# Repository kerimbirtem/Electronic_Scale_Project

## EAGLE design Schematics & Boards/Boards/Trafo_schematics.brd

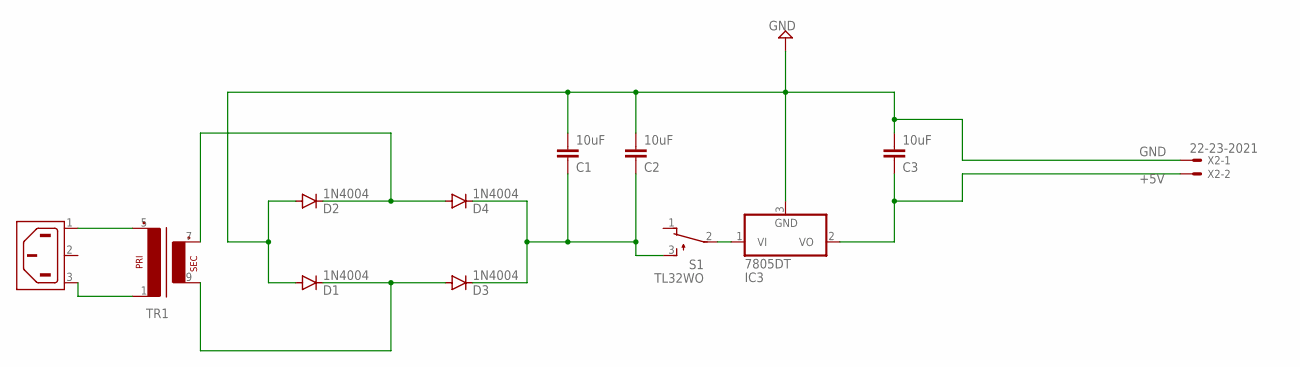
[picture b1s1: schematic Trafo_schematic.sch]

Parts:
C1, C2, C3: 10uF; C2.5-2
D1, D2, D3, D4: 1N4004; DO41-10
IC3: 7805DT; TO252
S1: TL32WO; TL3XWO
TR1: EI30-1
X1: 6ESRM-P
X2: 22-23-2021

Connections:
+5V: C3.1, IC3.2 (VO), X2.2
GND: C1.2, C2.2, C3.2, D1.A, D2.A, IC3.3 (GND), X2.1
unnamed: D1.C, D3.A, TR1.9 (S4)
unnamed: D2.C, D4.A, TR1.7 (S3)
unnamed: TR1.1, X1.3 (AC2)
unnamed: TR1.5 (P2), X1.1 (AC1)
unnamed: C1.1, C2.1, D3.C, D4.C, S1.3 (S)
unnamed: IC3.1 (VI), S1.2

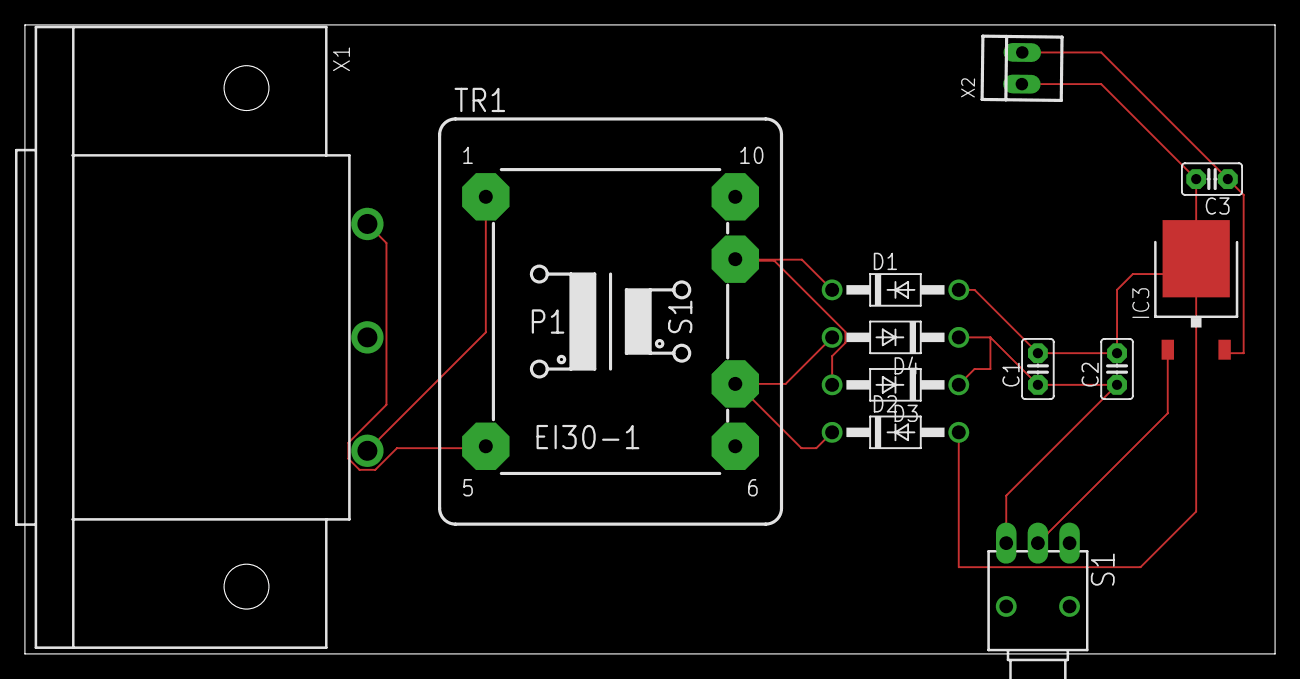
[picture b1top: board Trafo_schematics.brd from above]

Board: 2 copper layers, 100.3 x 50.5 mm, 12 parts (0 on the bottom side), 8 nets.

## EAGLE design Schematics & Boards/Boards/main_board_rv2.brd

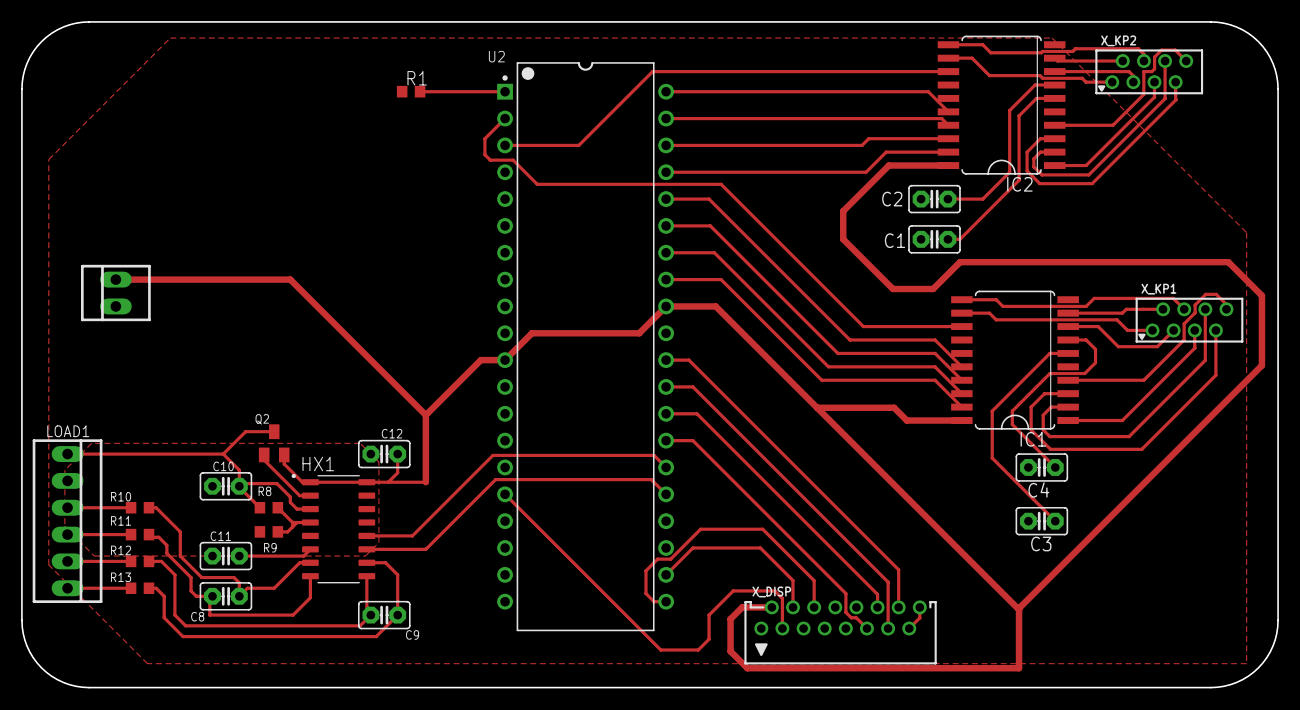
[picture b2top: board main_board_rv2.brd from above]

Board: 2 copper layers, 118.9 x 63.0 mm, 26 parts (0 on the bottom side), 55 nets.

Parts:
C1, C3, C8, C9, C11: 0.1uF; C2.5-2
C2, C4: 1 uF; C2.5-2
C10, C12: 10uF; C2.5-2
HX1: HX711; SOP127P600X180-16N
IC1, IC2: 74C922M; SO20W
LOAD1: 22-23-2061
Q2: SOT23
R1: 1k; R0603
R8: 20K; R0603
R9: 8.2K; R0603
R10, R11, R12, R13: 100; R0603
U2: MICROCHIP_PIC18F46K20-I-PMICROCHIP_PIC18F46K20-I-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; MICROCHIP_PIC18F46K20-I-P_0
X_DISP: FH21-16S-1DS
X_KP1, X_KP2: FH21-8S-1DSA
X_POWER: 22-23-2021

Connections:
+5V: C12.2, HX1.1, HX1.16, IC1.20, IC2.20, Q2.2, U2.11, U2.32, X_DISP.2, X_POWER.2
A+: LOAD1.4, R11.1
A-: LOAD1.3, R10.1
AVDD: C10.1, HX1.3, LOAD1.1, Q2.3, R8.1
B+: LOAD1.6, R13.1
B-: LOAD1.5, R12.1
CNTRST: U2.16, X_DISP.3
D4: U2.27, X_DISP.11
D5: U2.28, X_DISP.12
D6: U2.29, X_DISP.13
D7: U2.30, X_DISP.14
DT: HX1.12, U2.26
E: U2.21, X_DISP.6
GND: C1.2, C2.2, C3.2, C4.2, C10.2, C11.2, C12.1, HX1.5, HX1.14, HX1.15, IC1.10, IC1.14, IC2.10, IC2.14, LOAD1.2, R1.1, R9.1, U2.12, U2.31, X_DISP.1, X_DISP.5, X_DISP.7, X_DISP.8, X_DISP.9, X_DISP.10, X_POWER.1
unnamed: HX1.2, Q2.1
unnamed: IC2.12, X_KP2.1
unnamed: IC2.9, X_KP2.2
unnamed: IC2.8, X_KP2.3
unnamed: IC2.11, X_KP2.4
unnamed: IC2.1, X_KP2.5
unnamed: IC2.2, X_KP2.6
unnamed: IC2.3, X_KP2.7
unnamed: IC2.4, X_KP2.8
unnamed: IC1.12, X_KP1.1
unnamed: IC1.16, U2.36
unnamed: IC1.9, X_KP1.2
unnamed: IC1.8, X_KP1.3
unnamed: IC1.11, X_KP1.4
unnamed: HX1.4, R8.2, R9.2
unnamed: IC1.17, U2.35
unnamed: IC1.18, U2.34
unnamed: IC1.19, U2.33
unnamed: IC2.19, U2.37
unnamed: IC2.18, U2.38
unnamed: IC2.17, U2.39
unnamed: IC2.16, U2.40
unnamed: IC1.1, X_KP1.5
unnamed: IC1.2, X_KP1.6
unnamed: IC1.3, X_KP1.7
unnamed: IC1.4, X_KP1.8
unnamed: R1.2, U2.1
unnamed: C1.1, IC2.6
unnamed: C2.1, IC2.7
unnamed: C3.1, IC1.6
unnamed: C4.1, IC1.7
unnamed: C11.1, HX1.6
unnamed: C8.1, HX1.7, R10.2
unnamed: C8.2, HX1.8, R11.2
unnamed: C9.1, HX1.9, R12.2
unnamed: C9.2, HX1.10, R13.2
unnamed: IC1.13, U2.2
unnamed: IC2.13, U2.3
NC: X_DISP.15, X_DISP.16
RS: U2.22, X_DISP.4
SCK: HX1.11, U2.25

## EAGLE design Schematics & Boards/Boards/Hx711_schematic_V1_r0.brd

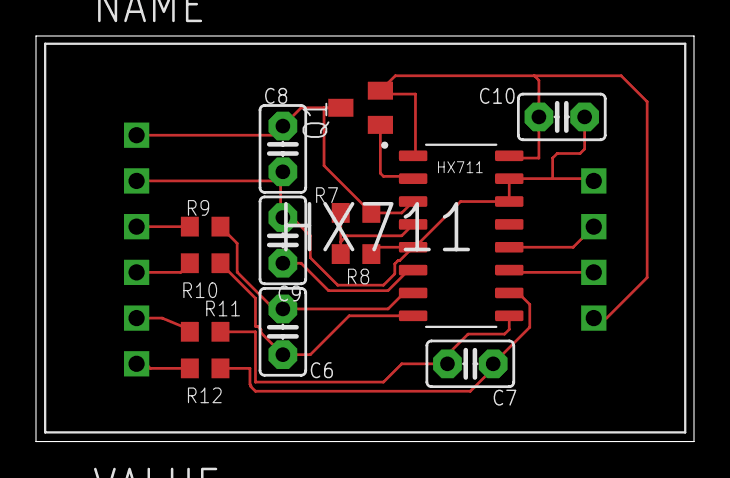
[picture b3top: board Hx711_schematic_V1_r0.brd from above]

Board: 2 copper layers, 36.6 x 22.5 mm, 14 parts (0 on the bottom side), 16 nets.

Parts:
C6, C7, C9: 0.1uF; C2.5-2
C8, C10: 10uF; C2.5-2
HX711: HX711; SOP127P600X180-16N
Q1: SOT23
R7: 20K; R0603
R8: 8.2K; R0603
R9, R10, R11, R12: 100; R0603
U$1: HX711

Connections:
+5V: C10.2, HX711.1, HX711.16, Q1.2, U$1.VCC
A+: R10.1, U$1.A+
A-: R9.1, U$1.A-
AVDD: C8.1, HX711.3, Q1.3, R7.1, U$1.E+
B+: R12.1, U$1.B+
B-: R11.1, U$1.B-
DT: HX711.12, U$1.DT
GND: C8.2, C9.2, C10.1, HX711.5, HX711.14, HX711.15, R8.1, U$1.E-, U$1.GND
unnamed: HX711.2, Q1.1
unnamed: HX711.4, R7.2, R8.2
unnamed: C6.1, HX711.7, R9.2
unnamed: C6.2, HX711.8, R10.2
unnamed: C7.1, HX711.9, R11.2
unnamed: C7.2, HX711.10, R12.2
unnamed: C9.1, HX711.6
SCK: HX711.11, U$1.SCK

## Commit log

2023-10-13 Create Datasheets
2023-10-13 Create asasa
2023-10-13 Create Schematics & Boards
2023-10-13 Create x
2023-10-13 Create s
2023-10-13 Create a
2023-10-13 Create b
